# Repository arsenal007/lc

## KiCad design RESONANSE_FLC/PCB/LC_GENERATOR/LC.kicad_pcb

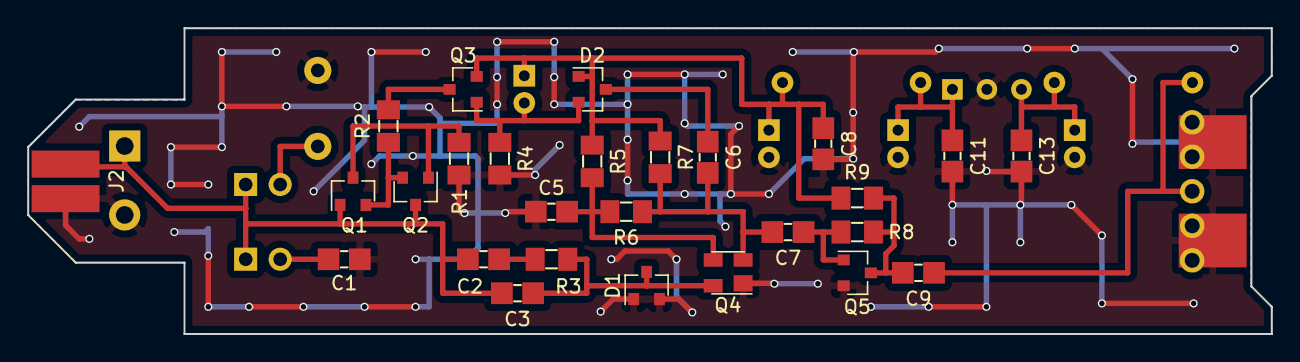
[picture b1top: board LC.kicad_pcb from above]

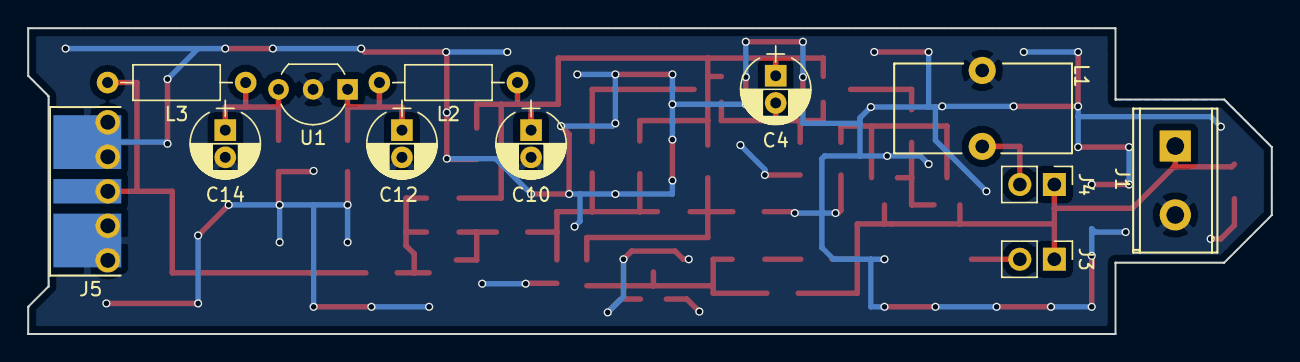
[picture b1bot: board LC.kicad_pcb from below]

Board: 2 copper layers, 91.5 x 22.5 mm, 39 parts (12 on the bottom side), 19 nets.

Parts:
C1: 100pF; C_1206_0603
C2, C5, C6, C7, C8, C9, C11, C13: 100nF; C_1206_0603
C3: 13; C_1206_0603
C4, C10, C12, C14: 10uF; CP_Radial_D5.0mm_P2.00mm
D1, D2: BAV99; SOT-23
J1: Conn_01x02; TerminalBlock_DG306-5.0_2pol
J2: Conn_01x02; SolderWirePad_double_SMD_2x5mm
J3, J4: Conn_01x02; Pin_Header_Straight_1x02_Pitch2.54mm
J5: RF; RFCONNECTOR
L1: 8uH*; Choke_Toroid_6,5x13mm_Vertical
L2, L3: 100uH; R_Axial_DIN0207_L6.3mm_D2.5mm_P10.16mm_Horizontal
Q1, Q2: BFT92; SOT-23
Q3: BC857; SOT-23
Q4: BF998; SOT-143
Q5: SS9018; SOT-23
R1: 10; R_1206_0603
R2, R3: 1k; R_1206_0603
R4, R8: 47k; R_1206_0603
R5, R6: 10k; R_1206_0603
R7: 330; R_1206_0603
R9: 470; R_1206_0603
U1: L78L05_TO92; TO-92_Inline_Wide

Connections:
GND: C1.2, C5.2, C8.2, C10.2, C11.2, C12.2, C13.2, C14.2, D1.1, D1.2, J1.2, J2.2, J5.2, L1.1, Q4.1, Q5.2, R1.2, R4.2, U1.2
unnamed: C1.1, J3.2
unnamed: C2.1, R3.2
unnamed: C2.2, C3.2, J1.1, J2.1, J3.1, J4.1, Q1.1, Q2.3
unnamed: C3.1, D1.3, Q4.4, R3.1
unnamed: C4.2, D2.2, Q3.1, R4.1
unnamed: C5.1, Q4.3, R5.2, R6.2
unnamed: C6.1, D2.3
unnamed: C6.2, C7.2, Q4.2, R6.1, R7.2
unnamed: C7.1, Q5.1, R8.1
unnamed: C9.1, J5.1, L3.2
unnamed: C9.2, Q5.3, R8.2, R9.2
unnamed: C4.1, C8.1, C10.1, D2.1, L2.1, Q3.2, R5.1, R7.1, R9.1
unnamed: C11.1, C12.1, L2.2, U1.1
unnamed: C13.1, C14.1, L3.1, U1.3
unnamed: J4.2, L1.2
unnamed: Q1.2, Q2.2, R2.1
unnamed: Q1.3, Q2.1, R1.1
unnamed: Q3.3, R2.2

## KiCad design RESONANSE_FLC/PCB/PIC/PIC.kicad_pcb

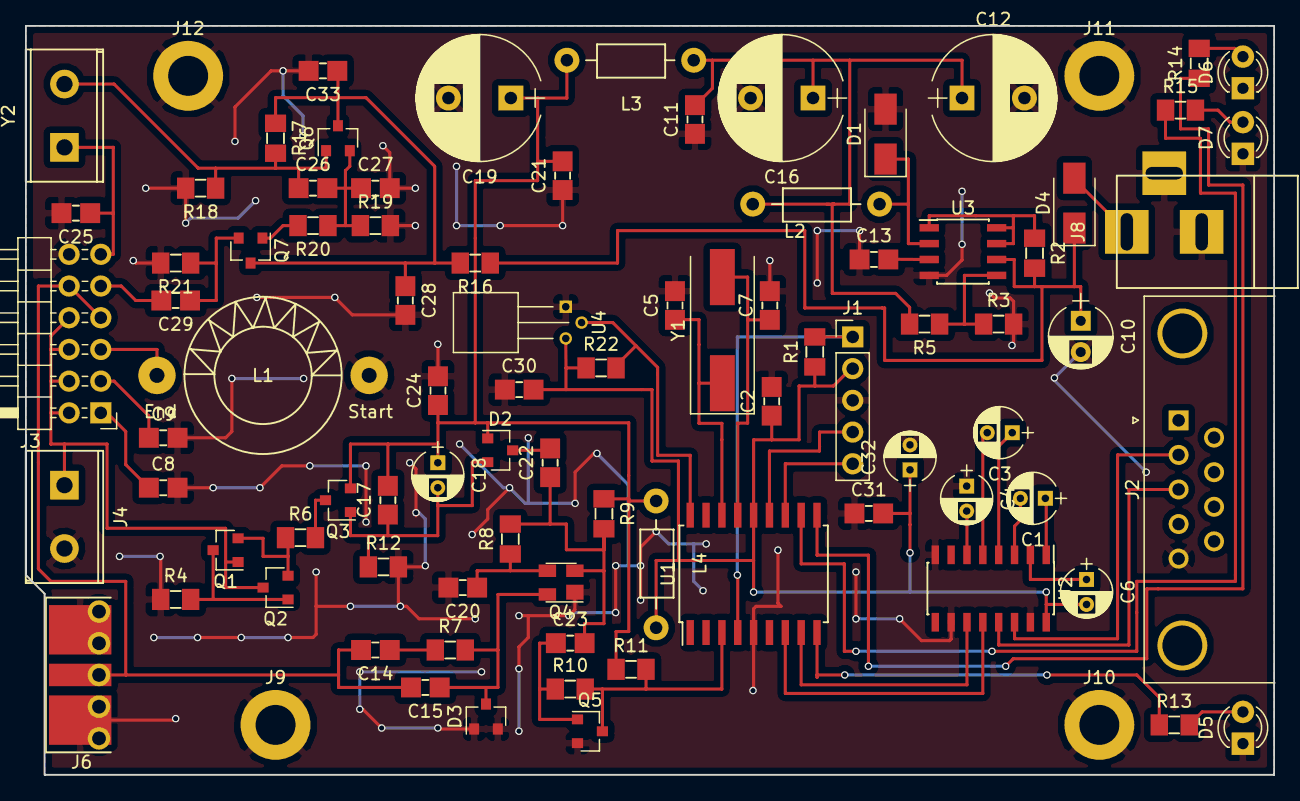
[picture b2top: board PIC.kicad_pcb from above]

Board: 2 copper layers, 100.0 x 60.0 mm, 89 parts (0 on the bottom side), 55 nets.

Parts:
C1, C3, C4, C6, C32: 1uF; CP_Radial_D4.0mm_P2.00mm
C2, C11, C14, C17, C20, C21, C22, C23, C24, C28, C29, C30, C31, C33: 100nF; C_1206_0603
C5, C7: 22pF; C_1206_0603
C8, C9: 100pF; C_1206_0603
C10: 100uF; CP_Radial_D5.0mm_P2.50mm
C12, C16, C19: 1000uF; CP_Radial_D10.0mm_P5.00mm
C13: 180pF; C_1206_0603
C15: 10pF; C_1206_0603
C18: 10uF; CP_Radial_D4.0mm_P2.00mm
C25: 33pF*; C_1206_0603
C26, C27: C_Small; C_1206_0603
D1, D4: SS14; D_SMA
D2, D3: BAV99; SOT-23
D5, D6, D7: LED; LED_D3.0mm
J1: ICSP; Pin_Header_Straight_1x05_Pitch2.54mm
J2: DB9_Female; DSUB-9_Female_Horizontal_Pitch2.77x2.84mm_EdgePinOffset4.94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
J3: FREQ; Pin_Header_Angled_2x06_Pitch2.54mm
J4: L/C; TerminalBlock_DG306-5.0_2pol
J6: Conn_Coaxial; RFCONNECTOR
J8: Jack-DC; BARREL_JACK
J9, J10, J11, J12: Conn_01x01; MountingHole_3.2mm_M3_DIN965_Pad
L1: 10uH; Choke_Toroid_horizontal_Diameter12-5mm_Amidon-T44
L2: 100uH; Choke_Horizontal_RM10mm
L3, L4: 280uH; Choke_Horizontal_RM10mm
Q1, Q2: BFT93; SOT-23
Q3: BC857; SOT-23
Q4: BF998; SOT-143
Q5: SS9018(J8); SOT-23
Q6, Q7: 2N3904; SOT-23
R1, R8: 10k; R_1206_0603
R2, R4: 10; R_1206_0603
R3, R6, R7, R13, R14, R15, R19, R20, R21, R22: 1k; R_1206_0603
R5: 3k; R_1206_0603
R9: 330; R_1206_0603
R10, R12: 47k; R_1206_0603
R11: 470; R_1206_0603
R16: 47; R_1206_0603
R17, R18: 100k; R_1206_0603
U1: PIC16(L)F628A-I/SO; SOIC-18W_7.5x11.6mm_Pitch1.27mm
U2: MAX232; SOIC-16_3.9x9.9mm_Pitch1.27mm
U3: MC34063; SOIC-8_3.9x4.9mm_Pitch1.27mm
U4: DS18B20; TO-92_Horizontal1_Molded_Narrow
Y1: 20Mhz; Crystal_SMD_HC49-SD
Y2: Crystal; TerminalBlock_DG306-5.0_2pol

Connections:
+5V: C2.1, C6.2, C30.2, C31.2, C32.1, J1.2, L4.2, R1.1, R22.1, U1.14, U2.16, U4.3
+5VA: C17.2, C18.1, C19.1, C21.2, C24.1, D2.1, L3.2, L4.1, Q3.2, R9.1, R11.1
+12V: C10.1, D4.1, R2.2, R16.1, U3.6
/MCU/ICSPCLK: J1.5, U1.12
/MCU/ICSPDAT: J1.4, U1.13
/MCU/VPP/~MCLR: J1.1, R1.2, U1.4
F: Q5.3, R10.2, R11.2, U1.3
FREQ: C14.2, C15.2, J3.7, J3.10, J6.1
G3UUR: C29.2, J3.9
G3UUR_F1F2: C25.1, J3.11, Y2.1
GND: C2.2, C4.1, C5.2, C7.2, C8.2, C9.2, C10.2, C11.1, C12.2, C13.1, C16.2, C19.2, C20.2, C21.1, C24.2, C25.2, C27.2, C28.2, C30.1, C31.1, C32.2, C33.2, D1.2, D3.1, D3.2, D5.1, D6.1, D7.1, J1.3, J2.5, J3.12, J4.2, J6.2, J8.2, J8.3, J9.1, J10.1, J11.1, J12.1, L1.1, Q4.1, Q5.2, R3.2, R4.1, R12.2, R18.2, R19.2, R21.2, U1.5, U2.8, U2.10, U2.15, U3.4, U4.1
unnamed: C1.1, U2.1
unnamed: C1.2, U2.3
unnamed: C3.1, U2.4
unnamed: C3.2, U2.5
unnamed: C4.2, U2.6
unnamed: C5.1, U1.16, Y1.1
unnamed: C6.1, U2.2
unnamed: C7.1, U1.15, Y1.2
unnamed: C8.1, J3.1
unnamed: C9.1, J3.3
unnamed: C11.2, C12.1, C16.1, L2.2, L3.1, R5.2
unnamed: C13.2, U3.3
unnamed: C14.1, R7.1
unnamed: C15.1, D3.3, Q4.4, R7.2
unnamed: C17.1, C18.2, D2.2, Q3.1, R12.1
unnamed: C20.1, Q4.3, R8.1
unnamed: C22.1, C23.2, Q4.2, R8.2, R9.2
unnamed: C22.2, D2.3
unnamed: C23.1, Q5.1, R10.1
unnamed: C26.1, Q6.1, R17.2, R18.1, Y2.2
unnamed: C26.2, C27.1, Q6.2, R19.1, R20.1
unnamed: C28.1, C33.1, Q6.3, Q7.3, R16.2, R17.1
unnamed: C29.1, Q7.2, R21.1
unnamed: D1.1, L2.1, U3.2
unnamed: D4.2, J8.1
unnamed: D5.2, R13.2
unnamed: D6.2, R14.2
unnamed: D7.2, R15.2
unnamed: J2.2, U2.14
unnamed: J2.3, U2.13
unnamed: J3.2, J3.4, J3.6, J3.8, J4.1, Q1.1, Q2.3
unnamed: J3.5, L1.2
unnamed: Q1.2, Q2.2, R6.1
unnamed: Q1.3, Q2.1, R4.2
unnamed: Q3.3, R6.2
unnamed: Q7.1, R20.2
unnamed: R2.1, U3.1, U3.7, U3.8
unnamed: R3.1, R5.1, U3.5
unnamed: R13.1, U1.9
unnamed: R14.1, U1.10
unnamed: R15.1, U1.11
unnamed: R22.2, U1.18, U4.2
unnamed: U1.7, U2.12
unnamed: U1.8, U2.11

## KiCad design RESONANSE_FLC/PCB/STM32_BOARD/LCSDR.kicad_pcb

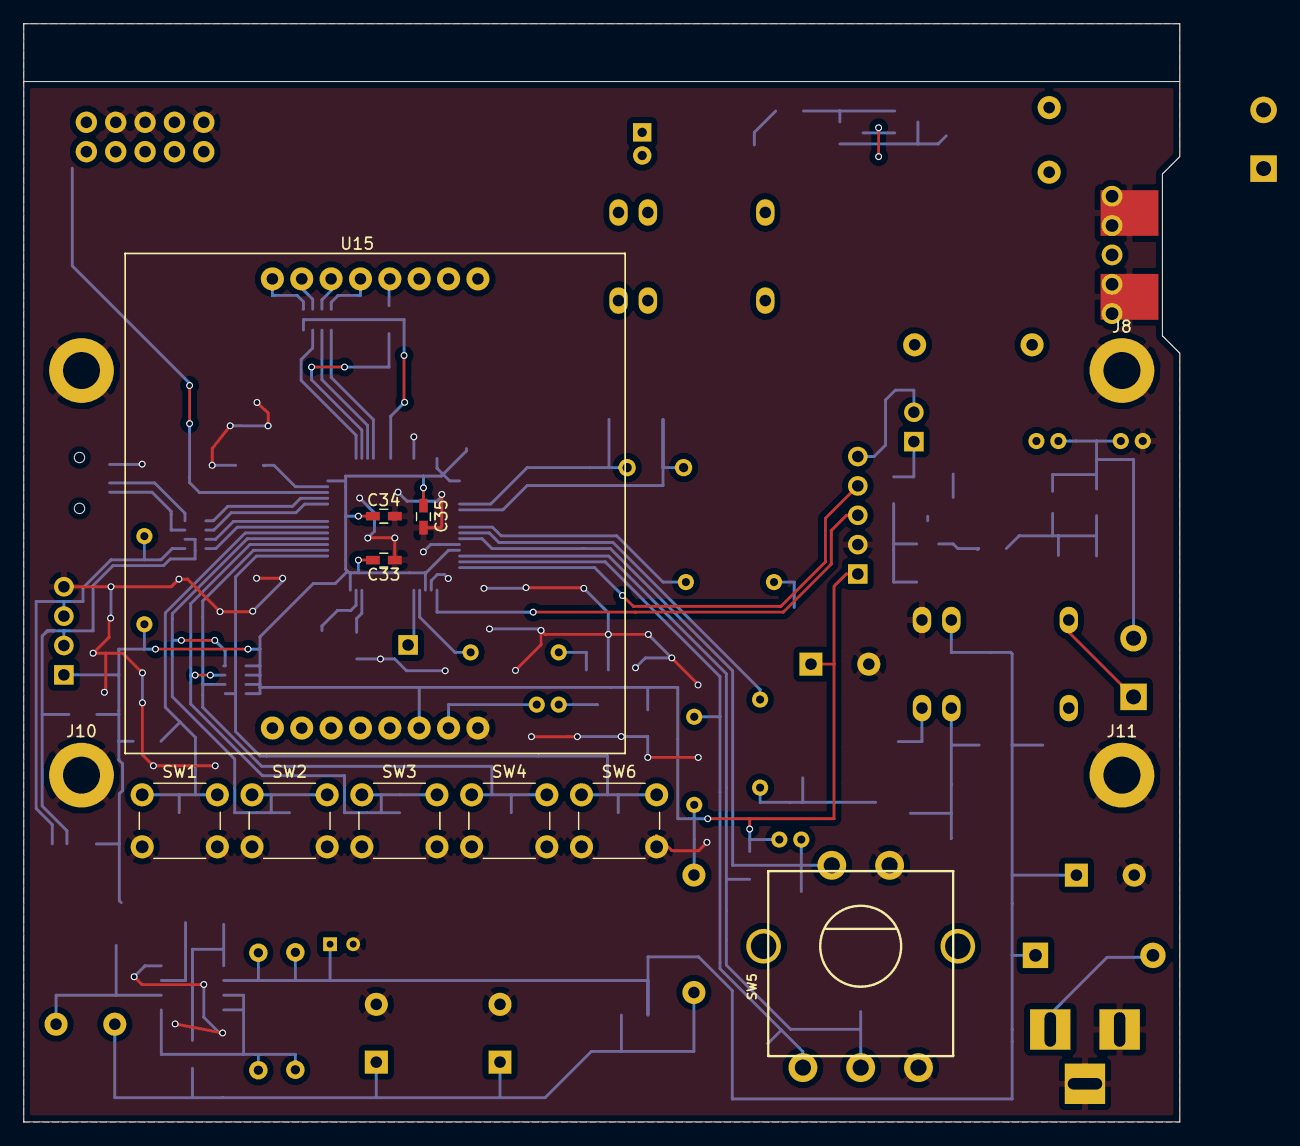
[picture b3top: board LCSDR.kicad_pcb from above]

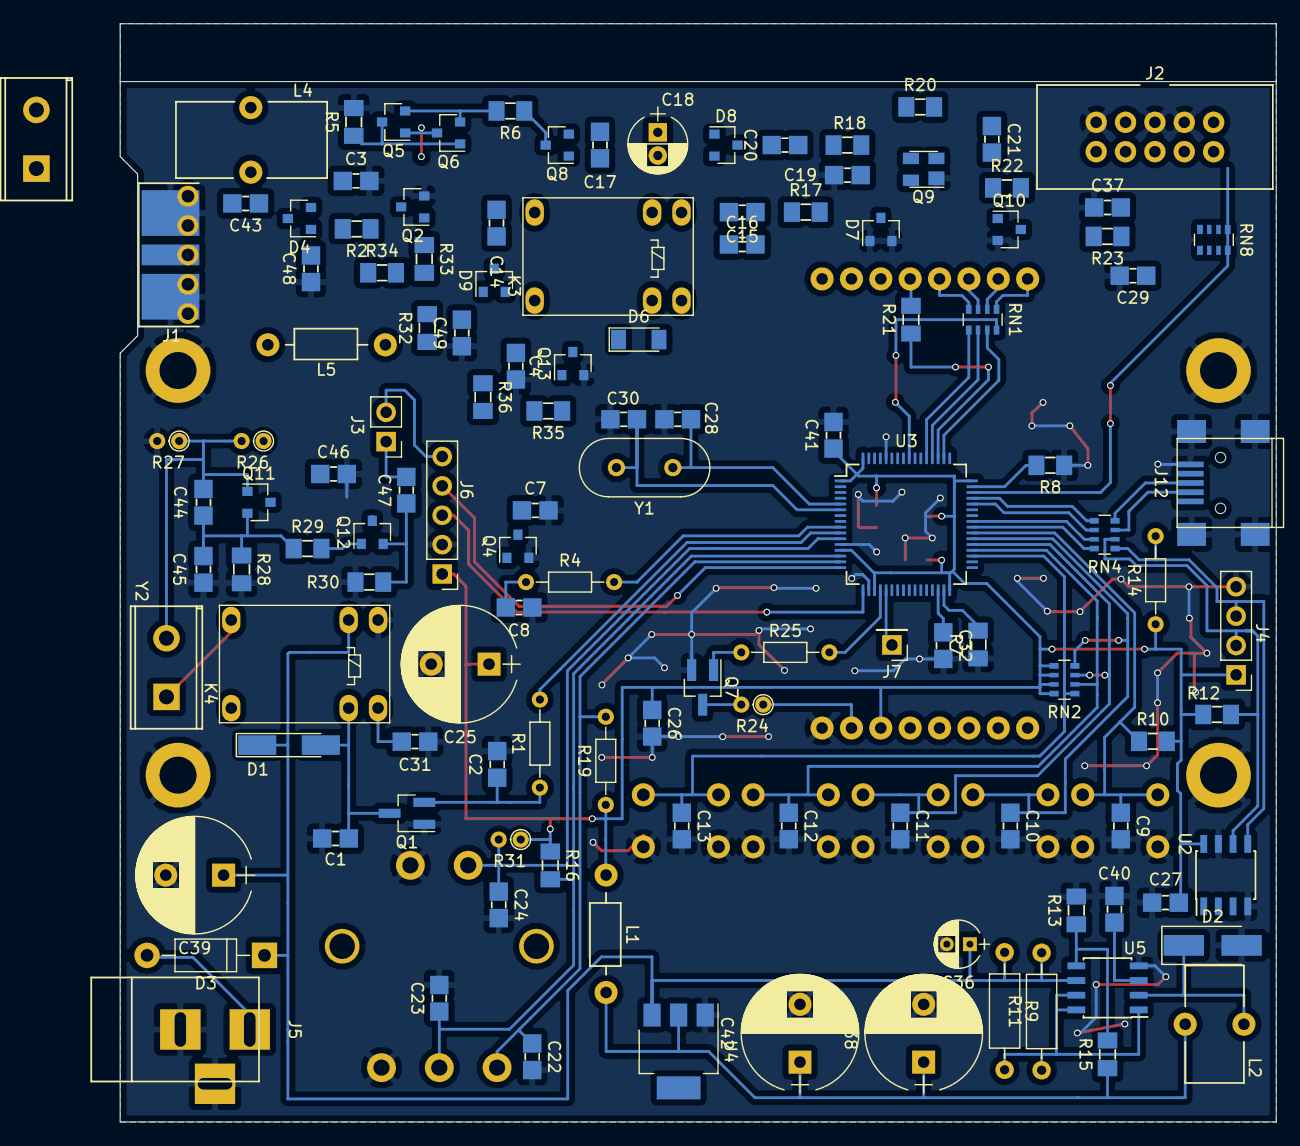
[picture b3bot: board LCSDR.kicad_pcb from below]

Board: 2 copper layers, 100.0 x 95.0 mm, 138 parts (124 on the bottom side), 93 nets.

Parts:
C1, C2, C3, C4, C7, C8, C9, C10, C11, C12, C13, C15, C17, C19, C20, C21, C22, C23, C24, C26, C27, C29, C32, C37, C41, C43, C46, C47, C48, C49: 100nF; C_1206_0603
C14, C44, C45: 100pF; C_1206_0603
C16: 13; C_1206_0603
C18: 10uF; CP_Radial_D5.0mm_P2.00mm
C25: 330uF; CP_Radial_D10.0mm_P5.00mm
C28, C30: 22; C_1206_0603
C31: 33pF; C_1206_0603
C33, C34, C35: 100nF; C_0603_HandSoldering
C36: 10uF; CP_Radial_D4.0mm_P2.00mm
C38, C39, C42: 1000uF; CP_Radial_D10.0mm_P5.00mm
C40: 200pF; C_1206_0603
D1: LL4148; D_MiniMELF_Handsoldering
D2: SS14; D_SMA_Handsoldering
D3: SS14; D_DO-41_SOD81_P10.16mm_Horizontal
D4, D7, D8, D9: BAV99; SOT-23
D6: LL4148; D_MiniMELF
J1: F; RFCONNECTOR
J2: IDC10 Serial Wire; USBBLASTER
J3: LC/G3UUR; Pin_Header_Straight_1x02_Pitch2.54mm
J4: Conn_01x04; Pin_Header_Straight_1x04_Pitch2.54mm
J5: Jack-DC; BARREL_JACK
J6: NEO-7M; Pin_Header_Straight_1x05_Pitch2.54mm
J7: Conn_01x01; Pin_Header_Straight_1x01_Pitch2.54mm
J8, J9, J10, J11: Conn_01x01; MountingHole_3.2mm_M3_DIN965_Pad
J12: USB_B_Mini; USB_Mini-B
K3, K4: TIANBO-HJR-4102-L; Relay_SPDT_HJR-4102
L1: 280uH; Choke_Horizontal_RM10mm
L2: 19uH; Choke_Toroid_5x10mm_Vertical
L3: Terminal; TerminalBlock_DG306-5.0_2pol
L4: 8uH; Choke_Toroid_6,5x13mm_Vertical
L5: 100uH; Choke_Horizontal_RM10mm
Q1: MMBT2222; SOT-23_Handsoldering
Q2, Q13: BC847; SOT-23
Q4: MMBT2222LT1G; SOT-23
Q5, Q6: BFT92; SOT-23
Q7: BC817; SOT-23_Handsoldering
Q8: BC857; SOT-23
Q9: BF998; SOT-143
Q10: SS9018(J8); SOT-23
Q11, Q12: SS9018; SOT-23
R1, R4: 2.7k; R_Axial_DIN0204_L3.6mm_D1.6mm_P7.62mm_Horizontal
R2, R18, R32: 10k; R_1206_0603
R5: 10; R_1206_0603
R6, R17, R28, R29, R30: 1k; R_1206_0603
R7, R8: 0*; R_1206_0603
R9, R11: 0.49R; R_Axial_DIN0207_L6.3mm_D2.5mm_P10.16mm_Horizontal
R10, R12, R16, R33, R35: 4.7k; R_1206_0603
R13: 11k; R_1206_0603
R14, R19: 4.7k; R_Axial_DIN0204_L3.6mm_D1.6mm_P7.62mm_Horizontal
R15: 18k; R_1206_0603
R20: 330; R_1206_0603
R21: 56R; R_1206_0603
R22: 36k; R_1206_0603
R23: 470; R_1206_0603
R24: 56R; R_Axial_DIN0204_L3.6mm_D1.6mm_P1.90mm_Vertical
R25: 56R; R_Axial_DIN0204_L3.6mm_D1.6mm_P7.62mm_Horizontal
R26: 100k; R_Axial_DIN0204_L3.6mm_D1.6mm_P1.90mm_Vertical
R27: 47k; R_Axial_DIN0204_L3.6mm_D1.6mm_P1.90mm_Vertical
R31: 4.7k; R_Axial_DIN0204_L3.6mm_D1.6mm_P1.90mm_Vertical
R34, R36: 220; R_1206_0603
RN1: 56R; R_Array_Convex_4x0603
RN2: 4.7k; R_Array_Convex_4x0603
RN4, RN8: 47; R_Array_Convex_4x0603
SW1, SW2, SW3, SW4, SW6: SW_Push_Dual; SW_PUSH_6mm_h13mm
SW5: ENCODER; SF-ROTARY-ENCODER
U2: FM24CL16B; SOIC-8_3.9x4.9mm_Pitch1.27mm
U3: STM32F401RCTx; LQFP-64_10x10mm_Pitch0.5mm
U4: AP1117-33; SOT-223
U5: MC34063; SOIC-8_3.9x4.9mm_Pitch1.27mm
U15: Nokia_5110_LCD; Nokia_5110-3310_LCD
Y1: 20Mhz; Crystal_HC49-U_Vertical
Y2: Crystal; TerminalBlock_DG306-5.0_2pol

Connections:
+3V3: C25.1, C26.1, C27.1, C33.2, C34.2, C35.2, C37.2, C41.1, J2.1, J4.1, J6.1, L1.2, R10.2, R12.1, R14.1, R16.1, R19.1, R23.1, R31.1, RN2.5, RN2.6, RN2.7, RN2.8, U2.8, U3.1, U3.13, U3.19, U3.32, U3.48, U3.64, U15.6
+12V: C17.1, C18.1, C36.1, C39.1, D1.1, D3.1, D6.1, D8.1, K3.8, K4.8, L5.2, Q8.2, R2.1, R9.1, R11.2, R20.1, R32.1, U4.3, U5.6
ADC: J7.1, U3.21
ENCODER_A: C23.1, R16.2, SW5.2, U3.14
ENCODER_B: C22.1, R19.2, SW5.1, U3.15
F_LC: Q10.3, R22.2, R23.2, U3.54
F_Q: C15.1, C16.1, J1.1, J3.2, J6.5, K3.6, L3.1
GND: C1.2, C2.2, C3.2, C4.2, C7.2, C8.2, C9.2, C10.2, C11.2, C12.2, C13.2, C19.1, C22.2, C23.2, C24.2, C25.2, C26.2, C27.2, C28.2, C29.2, C30.2, C31.2, C32.2, C33.1, C34.1, C35.1, C36.2, C37.1, C38.2, C39.2, C40.2, C41.2, C42.2, C45.2, C46.2, C48.1, C49.1, D2.2, D7.1, D7.2, J1.2, J2.3, J2.5, J2.9, J4.4, J5.2, J5.3, J6.2, J8.1, J9.1, J10.1, J11.1, J12.5, J12.6, K4.7, L3.2, Q1.1, Q2.2, Q4.2, Q7.2, Q9.1, Q10.2, Q13.2, R5.2, R7.1, R8.2, R13.2, R27.2, R28.2, R30.2, SW1.2, SW2.2, SW3.2, SW4.2, SW5.3, SW5.5, SW6.2, U2.4, U2.7, U3.12, U3.18, U3.60, U3.63, U4.1, U5.4, U15.8
I2C_SCL: J4.2, R12.2, RN4.2, U2.6
I2C_SCL_MCU: RN4.7, U3.41
I2C_SDA: J4.3, R14.2, RN4.1, U2.5
I2C_SDA_MCU: RN4.8, U3.40
KEY_A: C9.1, R10.1, SW1.1, U3.39
KEY_B: C10.1, RN2.4, SW2.1, U3.38
KEY_C: C11.1, RN2.3, SW3.1, U3.37
KEY_D: C12.1, RN2.2, SW4.1, U3.36
KEY_E: C13.1, RN2.1, SW6.1, U3.35
KEY_MENU: C24.1, R31.2, SW5.4, U3.11
LCD_CE: RN1.7, U3.50
LCD_CLK: R21.1, U3.51
LCD_DC: RN1.6, U3.52
LCD_DIN: RN1.5, U3.53
LCD_LIGHT: R25.2, U3.20
LCD_RESET: RN1.8, U3.56
MCU_RESET: C29.1, RN8.5, U3.7
unnamed: C2.1, Q1.2, R1.1
unnamed: C3.1, D4.2, Q2.3, R2.2
unnamed: C4.1, D9.2, Q13.3, R32.2
unnamed: C8.1, Q4.1, R4.1
unnamed: C14.1, K3.12, L4.1, Q5.1, Q6.3
unnamed: C14.2, D9.3
unnamed: C15.2, R17.1
unnamed: C16.2, D7.3, Q9.4, R17.2
unnamed: C17.2, C18.2, D8.2, Q8.1
unnamed: C19.2, Q9.3, R18.2
unnamed: C20.1, D8.3
unnamed: C20.2, C21.1, Q9.2, R18.1, R20.2
unnamed: C21.2, Q10.1, R22.1
unnamed: C28.1, U3.5, Y1.1
unnamed: C30.1, U3.6, Y1.2
unnamed: C31.1, K4.6
unnamed: C32.1, U3.30
unnamed: C38.1, C42.1, L1.1, L2.2, R15.1, U4.2
unnamed: C40.1, U5.3
unnamed: C43.1, D4.3
unnamed: C43.2, L4.2
unnamed: C44.1, Q11.1, R26.2, R27.1, Y2.2
unnamed: C44.2, C45.1, Q11.2, R28.1, R29.1
unnamed: C46.1, L5.1, Q11.3, Q12.3, R26.1
unnamed: C47.1, Q12.2, R30.1
unnamed: C47.2, J3.1
unnamed: C48.2, D4.1, R34.1
unnamed: C49.2, D9.1, R36.1
unnamed: D2.1, L2.1, U5.2
unnamed: D3.2, J5.1
unnamed: J2.2, RN8.1
unnamed: J2.4, RN8.2
unnamed: J2.6, RN8.3
unnamed: J2.10, RN8.4
unnamed: J12.2, RN4.3
unnamed: J12.3, RN4.4
unnamed: K4.12, Y2.1
unnamed: Q2.1, R33.1
unnamed: Q5.2, Q6.2, R6.2
unnamed: Q5.3, Q6.1, R5.1
unnamed: Q7.1, R25.1
unnamed: Q7.3, R24.2
unnamed: Q8.3, R6.1
unnamed: Q12.1, R29.2
unnamed: Q13.1, R35.1
unnamed: R7.2, U3.31
unnamed: R8.1, U3.47
unnamed: R9.2, R11.1, U5.1, U5.7, U5.8
unnamed: R13.1, R15.2, U5.5
unnamed: R21.2, U15.5
unnamed: R24.1, U15.7
unnamed: RN1.1, U15.1
unnamed: RN1.2, U15.2
unnamed: RN1.3, U15.3
unnamed: RN1.4, U15.4
REL_0: C7.1, D6.2, K3.5, Q4.3
REL_0_MCU: R4.2, U3.9
REL_1_MCU: R35.2, R36.2, U3.3
REL_2_MCU: R33.2, R34.2, U3.2
REL_3: C1.1, D1.2, K4.5, Q1.3
REL_3_MCU: R1.2, U3.10
SWCLK: RN8.7, U3.49
SWDIO: RN8.8, U3.46
SWO: RN8.6, U3.55
USART_RX: J6.3, U3.17
USART_TX: J6.4, U3.16
USB_DM: RN4.6, U3.44
USB_DP: RN4.5, U3.45

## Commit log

2019-08-12 first commit, measure Capicatance
2019-08-12 capicatance simplyfing
2019-08-13 add struct TExecute
2019-08-14 calibration
2019-08-20 first working version, without inductance tests
2019-08-22 more precise calibration, callback call per value
2019-08-22 cmake static
2019-08-22 Squashed 'cmake/' content from commit 38131f4
    git-subtree-dir: cmake
    git-subtree-split: 38131f4c7b0914b450c5d03396954629eb13c537
2019-08-22 dynamic library
2019-08-26 migrate to pure head C++ library
2019-08-26 lambda calls for _run(), mini circular buffer
2019-08-27 add example/C, continue *.hpp
2019-08-27 add examples, remove hid.c, hidapi.h
2019-08-28 some fold expression, RingBuffer default template arguments
2019-08-29 BUG(NEED TO FIX): Segmentation fault after reconect
2019-08-30 fix bug: more then one run thread
2019-09-04 staging by calibration
2019-09-04 console app, staging
2019-09-04 fix some bugs
2019-09-05 add wrapper over shared_future
2019-09-05 press ENTER to save, first static console app console/CMakeLists.txt
2019-09-06 TCLAP
2019-09-06 TLCAP, L_calibration
2019-09-09 bugs, pre release
2019-09-09 begin to separate in classes measure, calibrate. the same callback for C-,L- calibration
2019-09-12 working, not optimal
2019-11-07 add resonance FLC
2019-11-07 add uart pic16f628a example
2019-11-08 add PCB kicad project
2019-11-08 add cube STM32F103
2019-11-11 modified uart.asm
2019-11-13 last commit with PIC MCU
2019-11-14 first schematics
2019-11-14 footprints
2019-11-15 PCB work, enclosure 80x25x25
2019-11-16 finish PCB
2019-11-16 add BF998
2019-11-16 fix PCB VIA near D1
2020-01-13 add resonance FLC STM32 Board
2020-02-17 PIC PCB
2020-02-19 add comm.py
2020-02-20 add __init__ comm.py
